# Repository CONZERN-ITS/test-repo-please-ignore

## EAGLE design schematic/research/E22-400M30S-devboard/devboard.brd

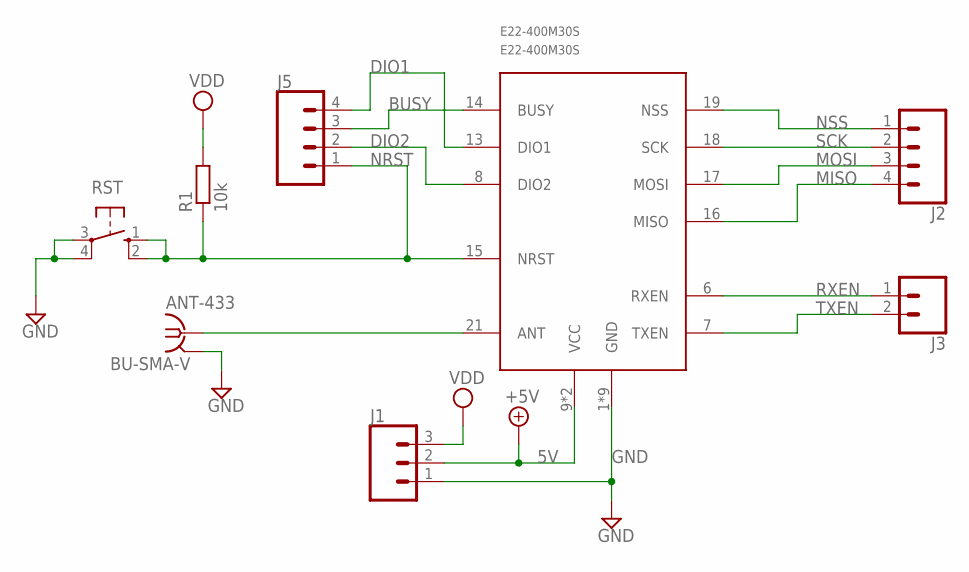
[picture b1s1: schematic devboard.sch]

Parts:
ANT-433: BU-SMA-V
E22-400M30S: E22-400M30S
J1: CONN_03LOCK_LONGPADS; 1X03_LOCK_LONGPADS
J2, J5: CONN_04LOCK_LONGPADS; 1X04_LOCK_LONGPADS
J3: CONN_02PTH3; 1X02_LONGPADS
R1: 10k; R0603
RST: 10-XX; B3F-10XX

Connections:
5V: E22-400M30S.9 (VCC), E22-400M30S.10 (VCC), J1.2
ANT: ANT-433.1, E22-400M30S.21 (ANT)
BUSY: E22-400M30S.14 (BUSY), J5.3
DIO1: E22-400M30S.13 (DIO1), J5.4
DIO2: E22-400M30S.8 (DIO2), J5.2
GND: ANT-433.2, ANT-433.3 (2), ANT-433.4 (2), ANT-433.5 (2), E22-400M30S.1 (GND), E22-400M30S.2 (GND), E22-400M30S.3 (GND), E22-400M30S.4 (GND), E22-400M30S.5 (GND), E22-400M30S.11 (GND), E22-400M30S.12 (GND), E22-400M30S.20 (GND), E22-400M30S.22 (GND), J1.1, RST.3, RST.4 (P1)
MISO: E22-400M30S.16 (MISO), J2.4
MOSI: E22-400M30S.17 (MOSI), J2.3
NRST: E22-400M30S.15 (NRST), J5.1, R1.1, RST.1 (S), RST.2 (S1)
NSS: E22-400M30S.19 (NSS), J2.1
RXEN: E22-400M30S.6 (RXEN), J3.1
SCK: E22-400M30S.18 (SCK), J2.2
TXEN: E22-400M30S.7 (TXEN), J3.2
VDD: J1.3, R1.2

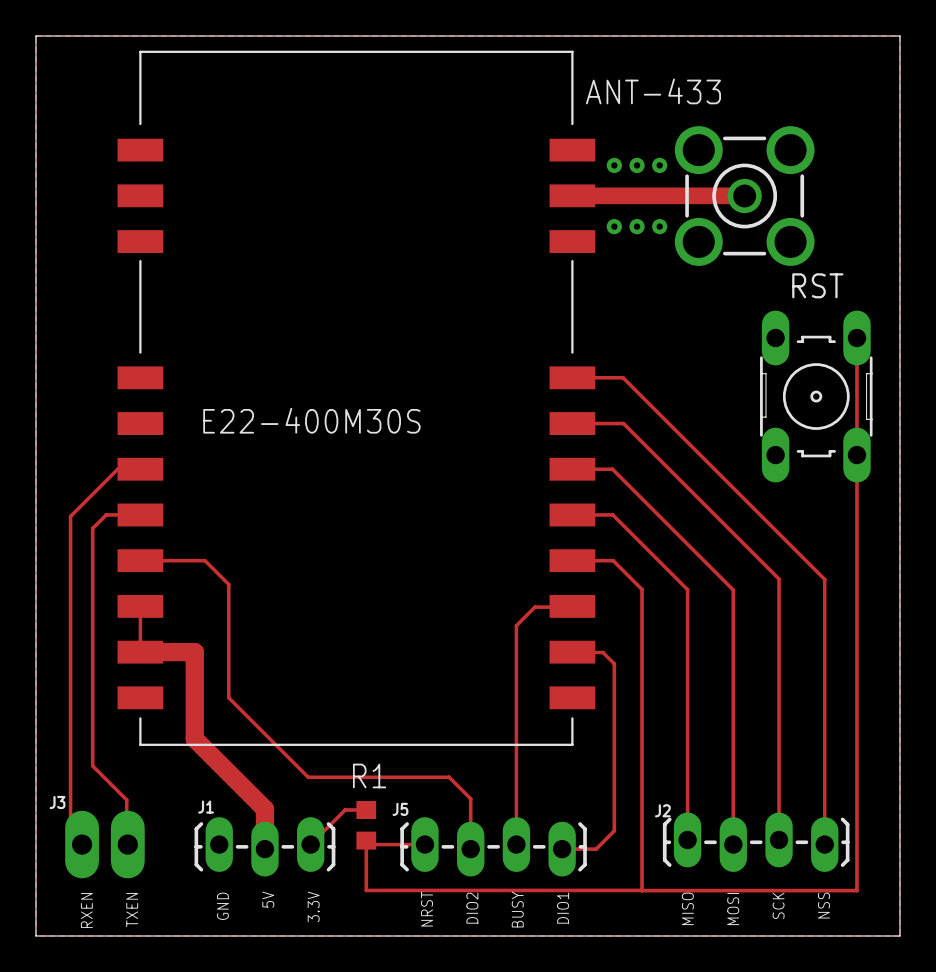
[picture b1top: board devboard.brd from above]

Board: 2 copper layers, 48.0 x 50.0 mm, 8 parts (0 on the bottom side), 14 nets.

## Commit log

2020-10-13 Плата разработчика для E22

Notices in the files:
parts and their libraries:
SparkFun-Connectors: Licensing: Creative Commons ShareAlike 4.0 International - https://creativecommons.org/licenses/by-sa/4.0
